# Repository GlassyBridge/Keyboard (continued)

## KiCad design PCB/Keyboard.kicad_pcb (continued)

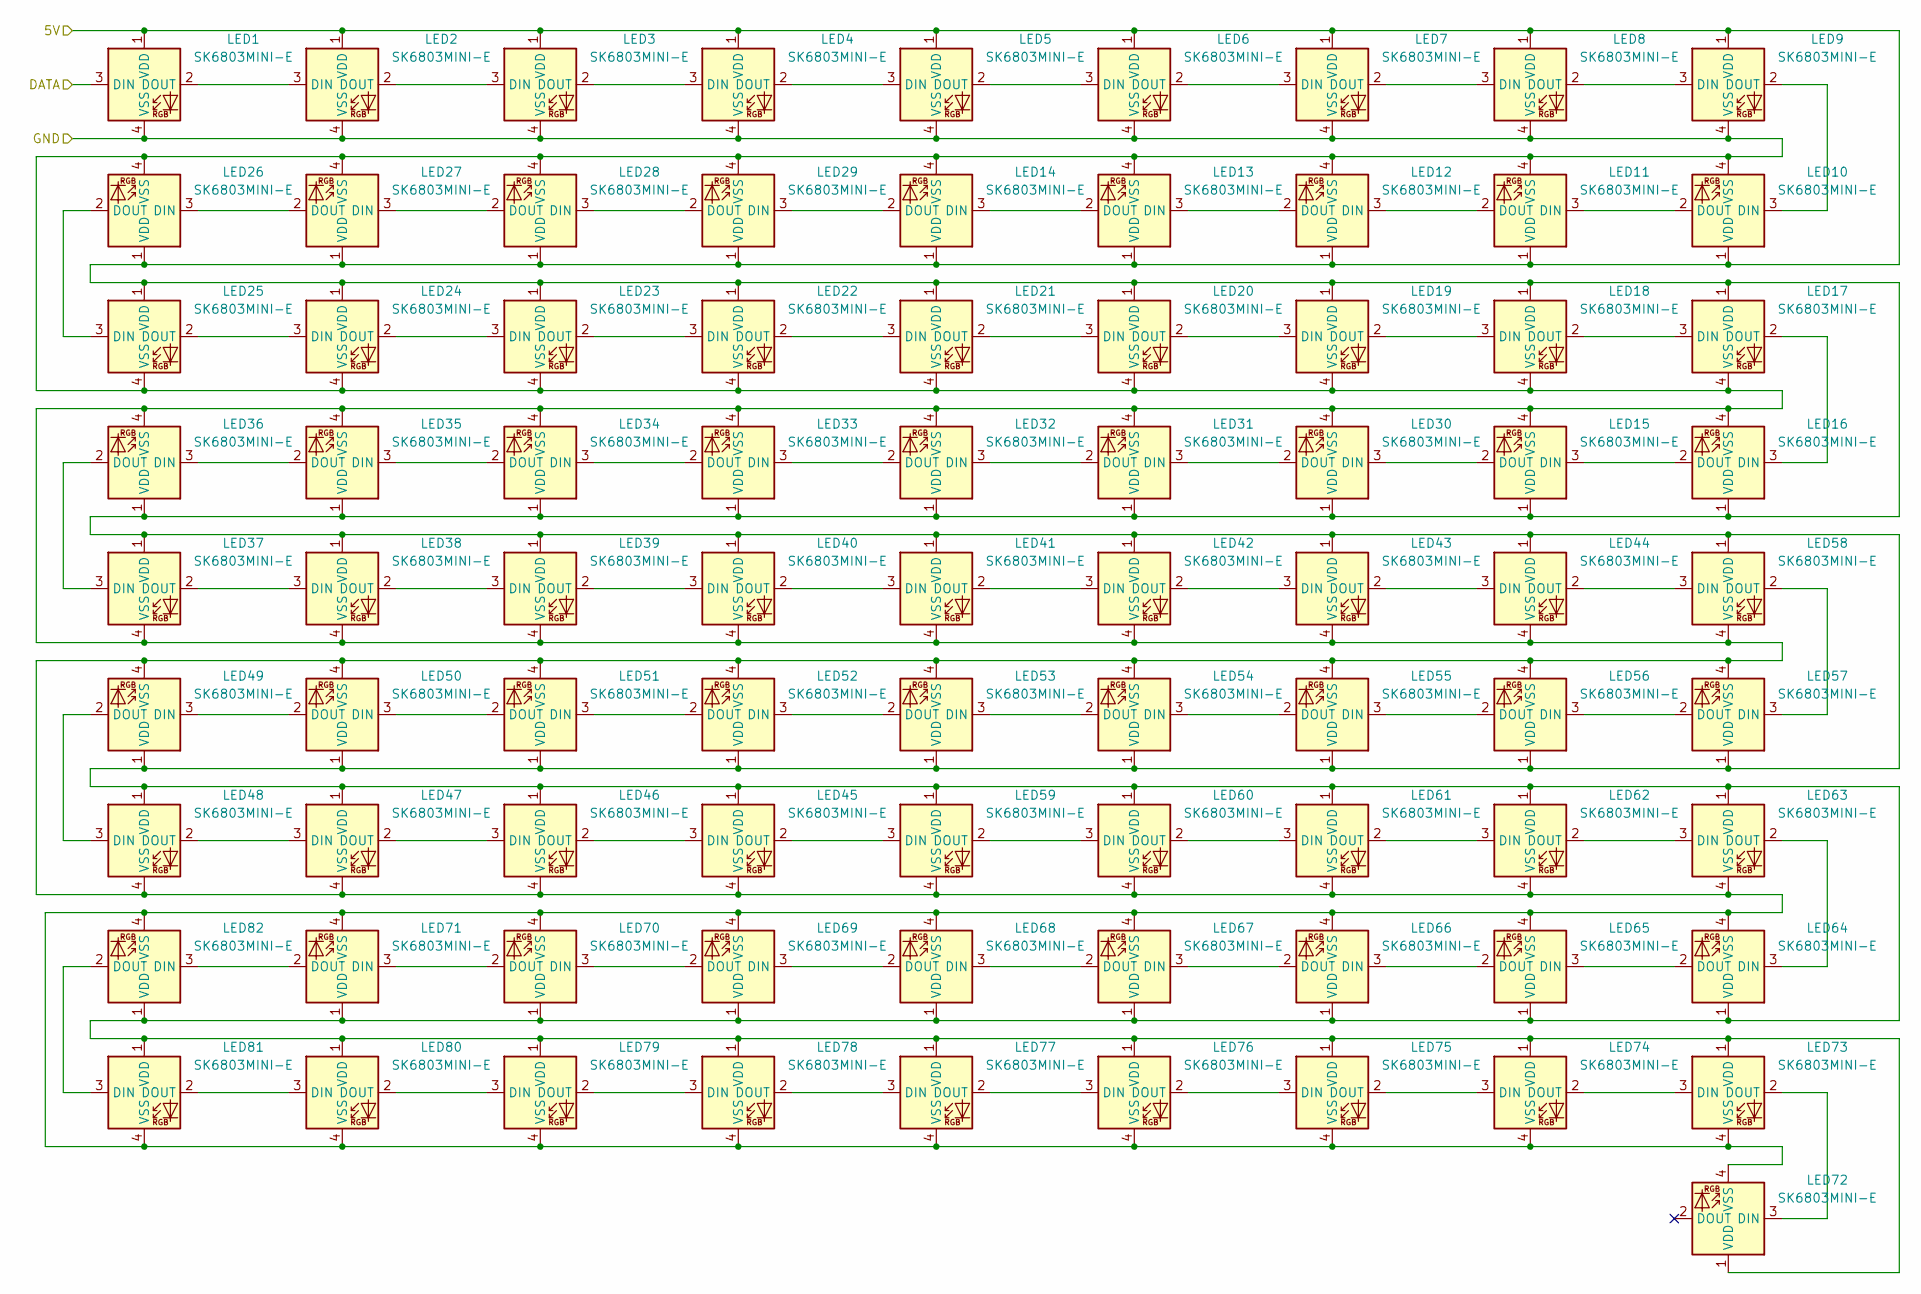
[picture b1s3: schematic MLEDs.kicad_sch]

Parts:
LED1, LED2, LED3, LED4, LED5, LED6, LED7, LED8, LED9, LED10, LED11, LED12, LED13, LED14, LED15, LED16, LED17, LED18, LED19, LED20, LED21, LED22, LED23, LED24, LED25, LED26, LED27, LED28, LED29, LED30, LED31, LED32, LED33, LED34, LED35, LED36, LED37, LED38, LED39, LED40, LED41, LED42, LED43, LED44, LED45, LED46, LED47, LED48, LED49, LED50, LED51, LED52, LED53, LED54, LED55, LED56, LED57, LED58, LED59, LED60, LED61, LED62, LED63, LED64, LED65, LED66, LED67, LED68, LED69, LED70, LED71, LED72, LED73, LED74, LED75, LED76, LED77, LED78, LED79, LED80, LED81, LED82: SK6803MINI-E; LED

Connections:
GND: LED1.4 (VSS), LED2.4 (VSS), LED3.4 (VSS), LED4.4 (VSS), LED5.4 (VSS), LED6.4 (VSS), LED7.4 (VSS), LED8.4 (VSS), LED9.4 (VSS), LED10.4 (VSS), LED11.4 (VSS), LED12.4 (VSS), LED13.4 (VSS), LED14.4 (VSS), LED15.4 (VSS), LED16.4 (VSS), LED17.4 (VSS), LED18.4 (VSS), LED19.4 (VSS), LED20.4 (VSS), LED21.4 (VSS), LED22.4 (VSS), LED23.4 (VSS), LED24.4 (VSS), LED25.4 (VSS), LED26.4 (VSS), LED27.4 (VSS), LED28.4 (VSS), LED29.4 (VSS), LED30.4 (VSS), LED31.4 (VSS), LED32.4 (VSS), LED33.4 (VSS), LED34.4 (VSS), LED35.4 (VSS), LED36.4 (VSS), LED37.4 (VSS), LED38.4 (VSS), LED39.4 (VSS), LED40.4 (VSS), LED41.4 (VSS), LED42.4 (VSS), LED43.4 (VSS), LED44.4 (VSS), LED45.4 (VSS), LED46.4 (VSS), LED47.4 (VSS), LED48.4 (VSS), LED49.4 (VSS), LED50.4 (VSS), LED51.4 (VSS), LED52.4 (VSS), LED53.4 (VSS), LED54.4 (VSS), LED55.4 (VSS), LED56.4 (VSS), LED57.4 (VSS), LED58.4 (VSS), LED59.4 (VSS), LED60.4 (VSS), LED61.4 (VSS), LED62.4 (VSS), LED63.4 (VSS), LED64.4 (VSS), LED65.4 (VSS), LED66.4 (VSS), LED67.4 (VSS), LED68.4 (VSS), LED69.4 (VSS), LED70.4 (VSS), LED71.4 (VSS), LED72.4 (VSS), LED73.4 (VSS), LED74.4 (VSS), LED75.4 (VSS), LED76.4 (VSS), LED77.4 (VSS), LED78.4 (VSS), LED79.4 (VSS), LED80.4 (VSS), LED81.4 (VSS), LED82.4 (VSS); also elsewhere on the board
M5V_LED: LED1.1 (VDD), LED2.1 (VDD), LED3.1 (VDD), LED4.1 (VDD), LED5.1 (VDD), LED6.1 (VDD), LED7.1 (VDD), LED8.1 (VDD), LED9.1 (VDD), LED10.1 (VDD), LED11.1 (VDD), LED12.1 (VDD), LED13.1 (VDD), LED14.1 (VDD), LED15.1 (VDD), LED16.1 (VDD), LED17.1 (VDD), LED18.1 (VDD), LED19.1 (VDD), LED20.1 (VDD), LED21.1 (VDD), LED22.1 (VDD), LED23.1 (VDD), LED24.1 (VDD), LED25.1 (VDD), LED26.1 (VDD), LED27.1 (VDD), LED28.1 (VDD), LED29.1 (VDD), LED30.1 (VDD), LED31.1 (VDD), LED32.1 (VDD), LED33.1 (VDD), LED34.1 (VDD), LED35.1 (VDD), LED36.1 (VDD), LED37.1 (VDD), LED38.1 (VDD), LED39.1 (VDD), LED40.1 (VDD), LED41.1 (VDD), LED42.1 (VDD), LED43.1 (VDD), LED44.1 (VDD), LED45.1 (VDD), LED46.1 (VDD), LED47.1 (VDD), LED48.1 (VDD), LED49.1 (VDD), LED50.1 (VDD), LED51.1 (VDD), LED52.1 (VDD), LED53.1 (VDD), LED54.1 (VDD), LED55.1 (VDD), LED56.1 (VDD), LED57.1 (VDD), LED58.1 (VDD), LED59.1 (VDD), LED60.1 (VDD), LED61.1 (VDD), LED62.1 (VDD), LED63.1 (VDD), LED64.1 (VDD), LED65.1 (VDD), LED66.1 (VDD), LED67.1 (VDD), LED68.1 (VDD), LED69.1 (VDD), LED70.1 (VDD), LED71.1 (VDD), LED72.1 (VDD), LED73.1 (VDD), LED74.1 (VDD), LED75.1 (VDD), LED76.1 (VDD), LED77.1 (VDD), LED78.1 (VDD), LED79.1 (VDD), LED80.1 (VDD), LED81.1 (VDD), LED82.1 (VDD); also elsewhere on the board
MLED_ctrl: LED1.3 (DIN); also elsewhere on the board
unnamed: LED1.2 (DOUT), LED2.3 (DIN)
unnamed: LED2.2 (DOUT), LED3.3 (DIN)
unnamed: LED3.2 (DOUT), LED4.3 (DIN)
unnamed: LED4.2 (DOUT), LED5.3 (DIN)
unnamed: LED5.2 (DOUT), LED6.3 (DIN)
unnamed: LED6.2 (DOUT), LED7.3 (DIN)
unnamed: LED7.2 (DOUT), LED8.3 (DIN)
unnamed: LED8.2 (DOUT), LED9.3 (DIN)
unnamed: LED9.2 (DOUT), LED10.3 (DIN)
unnamed: LED10.2 (DOUT), LED11.3 (DIN)
unnamed: LED11.2 (DOUT), LED12.3 (DIN)
unnamed: LED12.2 (DOUT), LED13.3 (DIN)
unnamed: LED13.2 (DOUT), LED14.3 (DIN)
unnamed: LED14.2 (DOUT), LED29.3 (DIN)
unnamed: LED15.3 (DIN), LED16.2 (DOUT)
unnamed: LED15.2 (DOUT), LED30.3 (DIN)
unnamed: LED16.3 (DIN), LED17.2 (DOUT)
unnamed: LED17.3 (DIN), LED18.2 (DOUT)
unnamed: LED18.3 (DIN), LED19.2 (DOUT)
unnamed: LED19.3 (DIN), LED20.2 (DOUT)
unnamed: LED20.3 (DIN), LED21.2 (DOUT)
unnamed: LED21.3 (DIN), LED22.2 (DOUT)
unnamed: LED22.3 (DIN), LED23.2 (DOUT)
unnamed: LED23.3 (DIN), LED24.2 (DOUT)
unnamed: LED24.3 (DIN), LED25.2 (DOUT)
unnamed: LED25.3 (DIN), LED26.2 (DOUT)
unnamed: LED26.3 (DIN), LED27.2 (DOUT)
unnamed: LED27.3 (DIN), LED28.2 (DOUT)
unnamed: LED28.3 (DIN), LED29.2 (DOUT)
unnamed: LED30.2 (DOUT), LED31.3 (DIN)
unnamed: LED31.2 (DOUT), LED32.3 (DIN)
unnamed: LED32.2 (DOUT), LED33.3 (DIN)
unnamed: LED33.2 (DOUT), LED34.3 (DIN)
unnamed: LED34.2 (DOUT), LED35.3 (DIN)
unnamed: LED35.2 (DOUT), LED36.3 (DIN)
unnamed: LED36.2 (DOUT), LED37.3 (DIN)
unnamed: LED37.2 (DOUT), LED38.3 (DIN)
unnamed: LED38.2 (DOUT), LED39.3 (DIN)
unnamed: LED39.2 (DOUT), LED40.3 (DIN)
unnamed: LED40.2 (DOUT), LED41.3 (DIN)
unnamed: LED41.2 (DOUT), LED42.3 (DIN)
unnamed: LED42.2 (DOUT), LED43.3 (DIN)
unnamed: LED43.2 (DOUT), LED44.3 (DIN)
unnamed: LED44.2 (DOUT), LED58.3 (DIN)
unnamed: LED45.3 (DIN), LED46.2 (DOUT)
unnamed: LED45.2 (DOUT), LED59.3 (DIN)
unnamed: LED46.3 (DIN), LED47.2 (DOUT)
unnamed: LED47.3 (DIN), LED48.2 (DOUT)
unnamed: LED48.3 (DIN), LED49.2 (DOUT)
unnamed: LED49.3 (DIN), LED50.2 (DOUT)
unnamed: LED50.3 (DIN), LED51.2 (DOUT)
unnamed: LED51.3 (DIN), LED52.2 (DOUT)
unnamed: LED52.3 (DIN), LED53.2 (DOUT)
unnamed: LED53.3 (DIN), LED54.2 (DOUT)
unnamed: LED54.3 (DIN), LED55.2 (DOUT)
unnamed: LED55.3 (DIN), LED56.2 (DOUT)
unnamed: LED56.3 (DIN), LED57.2 (DOUT)
unnamed: LED57.3 (DIN), LED58.2 (DOUT)
unnamed: LED59.2 (DOUT), LED60.3 (DIN)
unnamed: LED60.2 (DOUT), LED61.3 (DIN)
unnamed: LED61.2 (DOUT), LED62.3 (DIN)
unnamed: LED62.2 (DOUT), LED63.3 (DIN)
unnamed: LED63.2 (DOUT), LED64.3 (DIN)
unnamed: LED64.2 (DOUT), LED65.3 (DIN)
unnamed: LED65.2 (DOUT), LED66.3 (DIN)
unnamed: LED66.2 (DOUT), LED67.3 (DIN)
unnamed: LED67.2 (DOUT), LED68.3 (DIN)
unnamed: LED68.2 (DOUT), LED69.3 (DIN)
unnamed: LED69.2 (DOUT), LED70.3 (DIN)
unnamed: LED70.2 (DOUT), LED71.3 (DIN)
unnamed: LED71.2 (DOUT), LED82.3 (DIN)
unnamed: LED72.3 (DIN), LED73.2 (DOUT)
unnamed: LED73.3 (DIN), LED74.2 (DOUT)
unnamed: LED74.3 (DIN), LED75.2 (DOUT)
unnamed: LED75.3 (DIN), LED76.2 (DOUT)
unnamed: LED76.3 (DIN), LED77.2 (DOUT)
unnamed: LED77.3 (DIN), LED78.2 (DOUT)
unnamed: LED78.3 (DIN), LED79.2 (DOUT)
unnamed: LED79.3 (DIN), LED80.2 (DOUT)
unnamed: LED80.3 (DIN), LED81.2 (DOUT)
unnamed: LED81.3 (DIN), LED82.2 (DOUT)

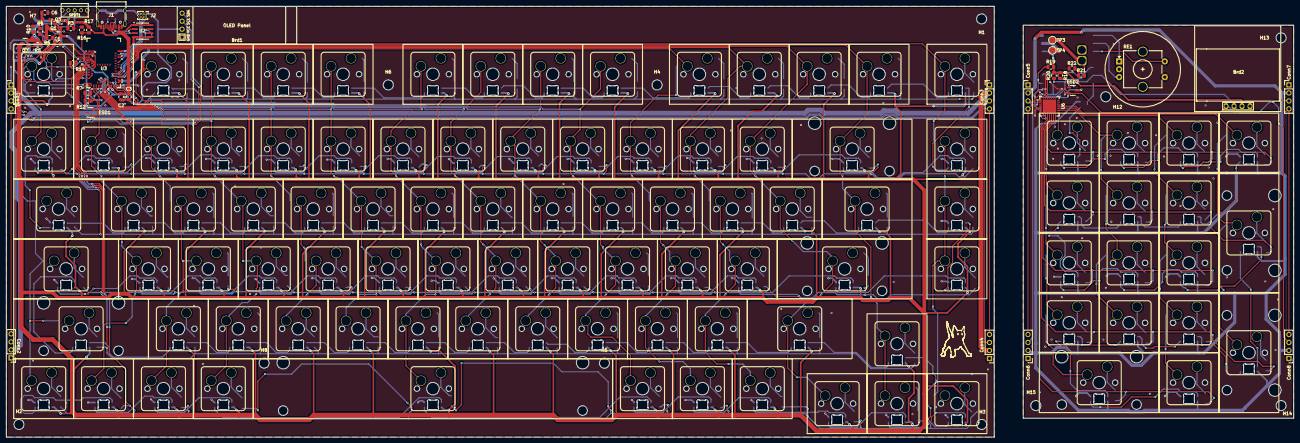
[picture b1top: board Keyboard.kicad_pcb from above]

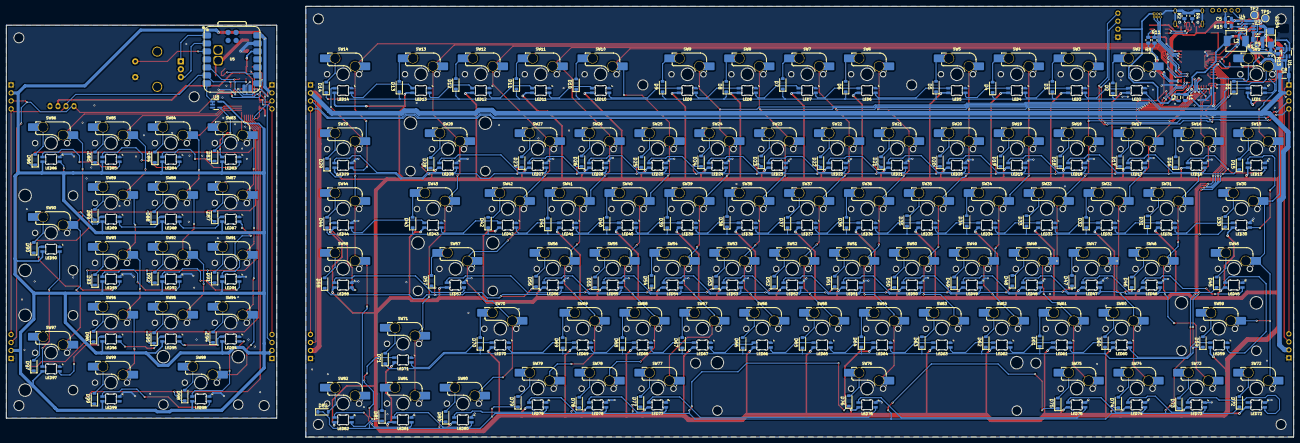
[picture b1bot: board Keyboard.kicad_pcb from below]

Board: 2 copper layers, 314.2 x 137.0 mm, 373 parts (318 on the bottom side), 270 nets.

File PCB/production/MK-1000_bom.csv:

Designator,Footprint,Quantity,Value,LCSC Part #
BRD1,OLED-TH_L38.0-W12.0_HS91L02W2C01,1,SH1106,
BRD2,128x64OLED,1,SH1106,
"C1, C2, C3, C4",0805,4,10uF,C15850
"C5, C6",0805,2,4.7uF,C1779
"C7, C8",1206,2,22uF,
"CONN1, CONN3, CONN5, CONN7",Pogopin_Conn_1x4_Female,4,Conn_01x04_Pin,
"CONN2, CONN4, CONN6, CONN8",Pogopin_Conn_1x4_Male,4,Conn_01x04_Pin,
"D1, D10, D11, D12, D13, D14, D15, D16, D17, D18, D19, D2, D20, D21, D22, D23, D24, D25, D26, D27, D28, D29, D3, D30, D31, D32, D33, D34, D35, D36, D37, D38, D39, D4, D40, D41, D42, D43, D44, D45, D46, D47, D48, D49, D5, D50, D51, D52, D53, D54, D55, D56, D57, D58, D59, D6, D60, D61, D62, D63, D64, D65, D66, D67, D68, D69, D7, D70, D71, D72, D73, D74, D75, D76, D77, D78, D79, D8, D80, D81, D82, D83, D84, D85, D86, D87, D88, D89, D9, D90, D91, D92, D93, D94, D95, D96, D97, D98, D99",D_SOD-123,99,D,C2099
"ESD1, ESD2",SOT-23-3,2,ESDA5V3L,C587142
J1,USB_C_Receptacle_HRO_TYPE-C-31-M-12,1,USB_C_Receptacle_USB2.0_14P,C165948
J2,PinHeader_2x03_P1.00mm_Vertical,1,Conn_02x03_Odd_Even,C6837603
L1,0805,1,10uH,
L2,IND-SMD_L7.1-W6.6,1,22uH,
"LED1, LED10, LED11, LED12, LED13, LED14, LED15, LED16, LED17, LED18, LED19, LED2, LED20, LED21, LED22, LED23, LED24, LED25, LED26, LED27, LED28, LED29, LED3, LED30, LED31, LED32, LED33, LED34, LED35, LED36, LED37, LED38, LED39, LED4, LED40, LED41, LED42, LED43, LED44, LED45, LED46, LED47, LED48, LED49, LED5, LED50, LED51, LED52, LED53, LED54, LED55, LED56, LED57, LED58, LED59, LED6, LED60, LED61, LED62, LED63, LED64, LED65, LED66, LED67, LED68, LED69, LED7, LED70, LED71, LED72, LED73, LED74, LED75, LED76, LED77, LED78, LED79, LED8, LED80, LED81, LED82, LED83, LED84, LED85, LED86, LED87, LED88, LED89, LED9, LED90, LED91, LED92, LED93, LED94, LED95, LED96, LED97, LED98, LED99",LED,99,SK6803MINI-E,
"Q1, Q2, Q3",SOT-23,3,Q_PMOS_GSD,C10487
R1,0805,1,110k,
"R10, R17, R22",0805,3,2M,C26112
"R11, R8",0805,2,27R,C17594
"R12, R18, R20, R7",0805,4,4K7,C17673
R13,0805,1,15k,
"R14, R19",0805,2,10K,C17414
R15,0805,1,2K,C17604
"R16, R21, R9",0805,3,806K,C2933502
"R2, R4",0805,2,5K1,C27834
"R3, R5, R6",0805,3,100K,C2933502
RE1,RotaryEncoder_Alps_EC11E-Switch_Vertical_H20mm_CircularMountingHoles,1,RotaryEncoder_Switch,
SPDT1,1825232-1,1,SW_SPDT,
SS34,SS34,1,D,
"SW1, SW10, SW11, SW12, SW13, SW14, SW15, SW16, SW17, SW18, SW19, SW2, SW20, SW21, SW22, SW23, SW24, SW25, SW26, SW27, SW29, SW3, SW31, SW32, SW33, SW34, SW35, SW36, SW37, SW38, SW39, SW4, SW40, SW41, SW42, SW44, SW46, SW47, SW48, SW49, SW5, SW50, SW51, SW52, SW53, SW54, SW55, SW56, SW58, SW6, SW60, SW61, SW62, SW63, SW64, SW65, SW66, SW67, SW68, SW69, SW7, SW71, SW72, SW73, SW74, SW75, SW77, SW78, SW79, SW8, SW80, SW81, SW82, SW83, SW84, SW85, SW86, SW87, SW88, SW89, SW9, SW91, SW92, SW93, SW94, SW95, SW96, SW99",MX_HS_1u,88,SW_Push,C5333465
"SW28, SW98",MX_HS_2u,2,SW_Push,C5333465
"SW30, SW43",MX_HS_1.5u,2,SW_Push,C5333465
"SW45, SW70",MX_HS_1.75u,2,SW_Push,C5333465
"SW57, SW59",MX_HS_2.25u,2,SW_Push,C5333465
SW76,MX_HS_6u,1,SW_Push,C5333465
"SW90, SW97",MX_HS_2u_90deg,2,SW_Push,C5333465
U1,SOT-23-6,1,MT3608,
U2,SOIC-8_3.9x4.9mm_P1.27mm,1,USB6B1,C283483
U3,Raytac_MDBT50Q,1,MDBT50Q-1MV2,C5118826
U4,SOT-23-5,1,MCP73831-2-OT,C424093
U5,modified-XIAO-nRF52840-SMD,1,XIAO-nRF52840-SMD,C37327670
U6,QFN-28-1EP_6x6mm_P0.65mm_EP4.25x4.25mm,1,MCP23017_ML,C639770
"U7, U8",SC-74A-5_1.55x2.9mm_P0.95mm,2,74LV1T08GV,

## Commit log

2025-10-19 First schematic design
2025-10-26 Finished the schematics without LEDs
2025-11-09 Rearranged the key matrix and rotated the MCP
2025-11-18 Add: mounting holes
2025-11-23 Add: modular connectors
2025-11-23 One last step before finalizing the KeyPad
2025-11-24 Finalized the keypad
2025-12-10 Main board layout
2025-12-27 Schematic checkpoint before I mess up the layout
2025-12-27 I gave up on the hotswao modularity thing
2025-12-31 Finished the main board's design
2026-01-01 Reduced the main keyboard's profile
2026-01-01 fix issues with LTC4217
2026-01-05 Restructure file base and update README.md
2026-01-05 Added Keypad module
2026-01-06 Add: Production files
2026-01-06 Fic: Production files
2026-01-18 Simplified design to reduce cost
2026-01-21 Move: SMD components to top layer to reduce PCBA costs
2026-01-30 Update README and production file
2026-01-30 Move: Diodes to the back side
    Since I'm not getting PCBA now, I moved the diodes back to the back side of the PCB since I plan to make a keyboard plate because it keeps the dirt off and is aesthetically pleasing.
2026-01-30 Update: production files
2026-01-30 Edit: component in README.md
    Updated the link and details for the XIAO-nrf52840
2026-01-30 Edit: USB6B1 part number and link in README
    Updated the part number for USB6B1 to USB6B1RL
2026-02-01 Update BOM
    Changed component sourcing and added some components
2026-02-01 Update: Readme and PCB layout
2026-02-01 Production files
    Remo ed .csv from gitignore
2026-02-01 Update README.md
    Updated firmware section to indicate availability and added a note about the keyboard case.
2026-02-01 Add: BOM to the root directory to comply with blueprint's submission guidelines
2026-02-10 Update: Schematic and mainboard PCB
2026-02-11 Add: 3D models
2026-02-24 Update: schematic and PCB
    Replaced the MT3608 module with a custom circuit for it.
2026-03-01 Update: change footprint to V1V2, update 3D models, Add rotary encoder and 128x32 OLED, Remove second 128x64 OLED
2026-03-15 Update: Changed keyswitch footprints to HS MX switches
2026-03-15 Init: Keyboard Case
    Development only
2026-03-28 Update images
2026-03-28 Update: CAD
2026-03-28 Update README.md
    Updated images and modified switch type in the description.
2026-03-28 Update README.md
    Updated the schematic images
2026-03-29 Add: Keyboard_case.step
    Renamed Keypad_case.glb.step => Keypad_case.step
2026-03-29 Update README.md
    to reflect new changes
2026-03-29 Update README.md
    Case image
2026-04-01 Update: Added total cost and separated gerber files.
2026-04-01 Add: f3d files
    And updated readme to add a section where I explain about why this project was made as per submission guidelines.
2026-04-01 Update README.md
    Added battery connection wiring diagram
